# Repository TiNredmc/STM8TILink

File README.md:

# STM8TILink
The TI grey link clone based on arduino code and half duplex code for stm8s (credits after this line). WIP

# credit 
[DSchndr](https://github.com/DSchndr/serial2ti83) fork of [jw0k repo](https://github.com/jw0k/serial2ti83).

# PCB (at OSHpark).
[rev1 PCB](https://oshpark.com/shared_projects/LCwtGfEf).

# Extra
Due to the physical limitation of STM8S001J3 available pin. I was forced to use the single wire bi-directional UART. which it means that I share TX and RX on same pin (based on [This guy work](http://ficara.altervista.org/?p=4047&doing_wp_cron=1633419018.3038520812988281250000)). The problem starts when host send data to CH330N, since the TX is  connected to schottky barrier diode on cathod side, anode side is connected to STM8 (with 4.7k pull up) and RX pin of CH330N. The loopback "echo" occured everytime the host send command to STM8. The CH330N doesn't ignore the RX line when TX is transmitting. SO the host confused that the RX data is valid (which is not!). In order to solve this problem. I redesigned the PCB with included the SN74LVC1G3157DBVR, SPDT analog switch. I use this IC for bus isolation. CH330N RX will be isolated when MCU isn't send any data to host, it will left unconnected all the time to prevent the loopback echo and confuse host device.

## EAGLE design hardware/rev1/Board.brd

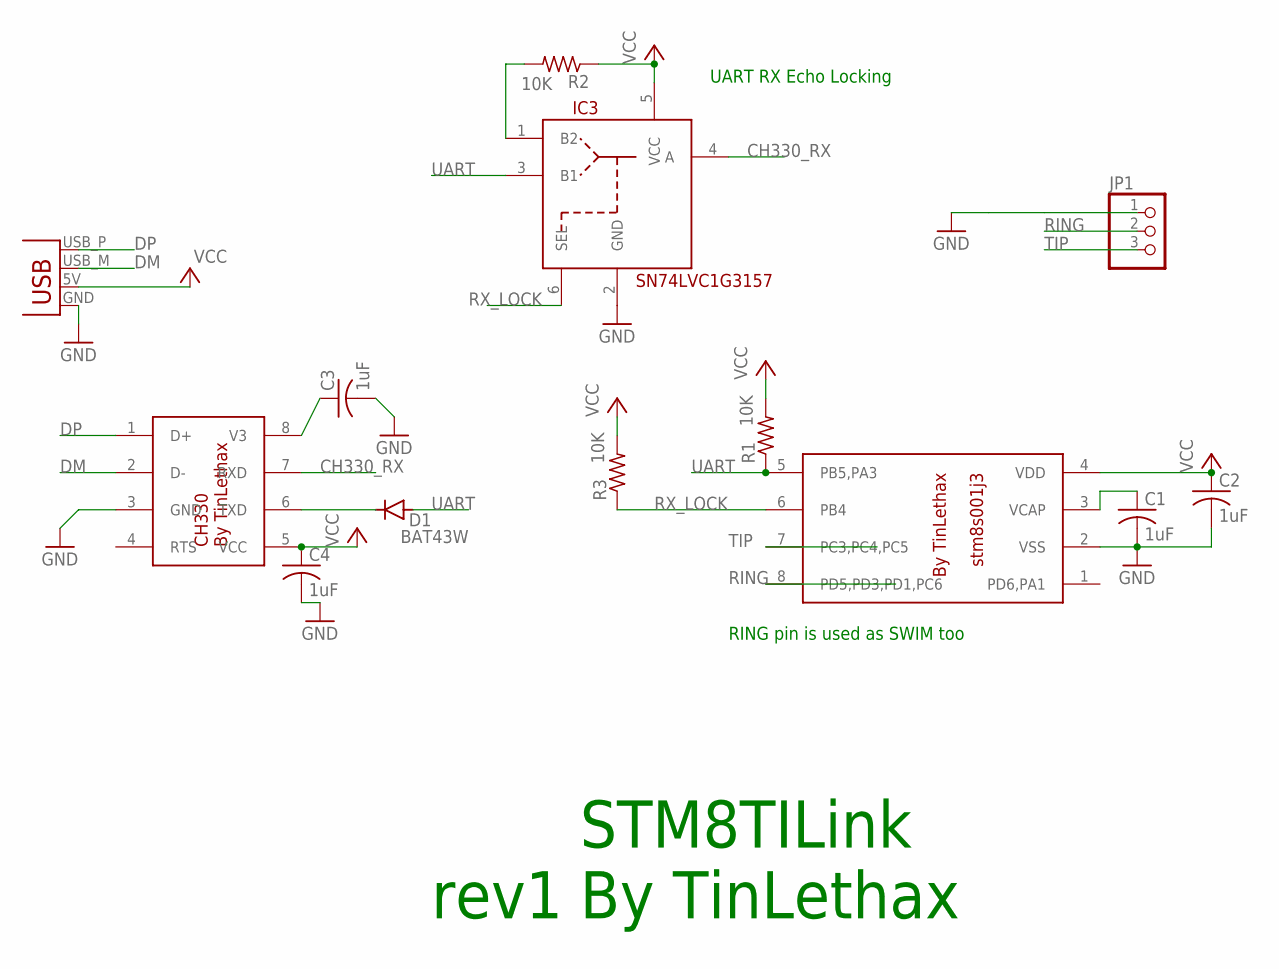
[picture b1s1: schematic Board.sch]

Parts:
C1, C2, C3, C4: 1uF; C0603
D1: BAT43W; SOD-123_MINI-SMA
IC1: STM8S001J3; SOP8
IC2: CH330; SOIC127P600X150-8N
IC3: SN74LVC1G3157; SOT95P280X145-6N
JP1: PINHD-1X3; 1X03
R1, R2, R3: 10K; R0603
X1: USB_USBPCB; USB_USB-A-PCB

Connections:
CH330_RX: IC2.7 (RXD), IC3.4 (A)
DM: IC2.2 (D-), X1.USB_M (D-)
DP: IC2.1 (D+), X1.USB_P (D+)
GND: C1.2, C2.2, C3.2, C4.2, IC1.2 (VSS), IC2.3 (GND), IC3.2 (GND), JP1.1, X1.GND
unnamed: C1.1, IC1.3 (VCAP)
unnamed: IC3.1 (B2), R2.2
unnamed: C3.1, IC2.8 (V3)
unnamed: D1.C, IC2.6 (TXD)
RING: IC1.8 (PD5,PD3,PD1,PC6), JP1.2
RX_LOCK: IC1.6 (PB4), IC3.6 (SEL), R3.1
TIP: IC1.7 (PC3,PC4,PC5), JP1.3
UART: D1.A, IC1.5 (PB5,PA3), IC3.3 (B1), R1.1
VCC: C2.1, C4.1, IC1.4 (VDD), IC2.5 (VCC), IC3.5 (VCC), R1.2, R2.1, R3.2, X1.5V (VBUS)

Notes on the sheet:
STM8TILink By TinLethax
RING pin is used as SWIM too
rev1
UART RX Echo Locking

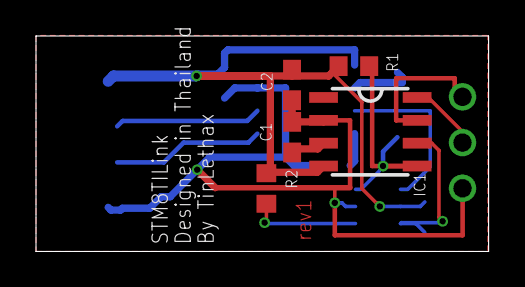
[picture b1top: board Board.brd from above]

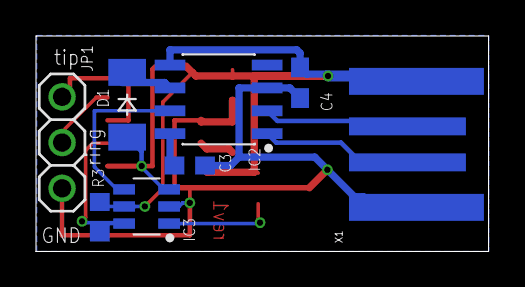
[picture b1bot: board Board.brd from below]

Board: 2 copper layers, 25.1 x 12.0 mm, 13 parts (8 on the bottom side), 13 nets.

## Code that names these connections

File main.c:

////////////////////////////////////////////////////////////////////////////////
// FW_VERSION  180701 (yymmdd) - Author: Emilio P.G. Ficara
// Modified to use with STM8TI by TinLethax
// V180701

#include <stm8s.h> // DO NOT USE here generic iostm8s.h (register map is different)
#include <delay.h>
#include <stdint.h>
#include <stdbool.h>

/* TIM4 stuffs */
// arr value for TIM4 millis() interupt.
#define TOP1MS		124 // Tim4 compare top value for 1mS tick
// millis() return value
volatile uint16_t mil = 0;
uint16_t millis(void);

/* UART stuffs */
volatile uint8_t echo = 0; // flag for "RX data is echo of TX"
volatile uint8_t DataFlag = 0;
volatile uint8_t revDat[4] = {0}; //data receive over the UART

/* variables for TI stuffs */

const uint8_t TIP = 5; //PC5 Tip pin
const uint8_t RING = 6; //PC6 Ring pin
const uint8_t TXTIMEOUT = 70; //50ms
const uint8_t RXTIMEOUT = 40; //20ms


#define TI_TIP_IS_HIGH   (PC_IDR & 0x10) 
#define TI_RING_IS_HIGH (PC_IDR & 0x20)

#define TI_TIP_IS_LOW   (~PC_IDR & 0x10)
#define TI_RING_IS_LOW  (~PC_IDR & 0x20)

void TiTipLow(){
	PC_ODR &= ~(1 << TIP);   
}

void TiRingLow(){
	PC_ODR &= ~(1 << RING);   
}

void TiTipOutput(){
	PC_DDR |= (1 << TIP);
	PC_CR1 |= (1 << TIP);
}

void TiRingOutput(){
	PC_DDR |= (1 << RING);
	PC_CR1 |= (1 << RING);
}

void TiTipInputHigh(){
	PC_DDR &= ~(1 << TIP);
	PC_CR1 |= (1 << TIP);
}

void TiRingInputHigh(){
	PC_DDR &= ~(1 << RING);
	PC_CR1 |= (1 << RING);
}


//------------------------------------------------------------------------------
// Serial COMM section

void OutCom(unsigned char c)// sending single byte from calc to PC
{
	echo = 1; // set echo flag (TX will be immediatly received on RX)
	while((UART1_SR & 0x80) == 0); // wait for TXE = 1
	UART1_DR = c; // send char
	while(echo); // wait until echo received
}

//------------------------------------------------------------------------------
// Interrupts section
//
void tim4_millis_irq(void) __interrupt(23)// The millis part, every 1 ms
{
     TIM4_SR = 0x00; // clear irq flag
     mil++;
}

void USART1_RX(void) __interrupt(18){ // Deal with the incoming data from PC and soon will transfer to calc

uint8_t e;

	e = UART1_SR; // read / clear (and ignore) error flags
	e = 1;
	revDat[0] = UART1_DR; // get the char and clear irq
	if(echo){ // if received data is echo of TX
		echo = 0; // turn off flag and don't save
	}else{
		while(UART1_SR & 0x20)// wait until buffer is empty
		revDat[e++] = UART1_DR;// reading all data from host.
		
		DataFlag = 1;// incoming data is not echo but it's data to send to Ti calc.
	}

}

////////////////////////////////////////////////////////////////////////////////
// Stuff for millis(); and TI stuff
//
uint16_t millis(){
return (uint16_t)mil;
}

void sendByte(uint8_t byte){
    uint16_t currentTime;

    for (uint8_t i = 0; i < 8; ++i){
        bool bit = byte & 0x01;
        byte >>= 1;

        //poll both lines until they are both high, which means we're ready to send a bit
        currentTime = millis();
        while (TI_TIP_IS_LOW || TI_RING_IS_LOW){
            if (millis() - currentTime > TXTIMEOUT){
                return;
            }
        }

        if (bit){
            // send a bit by pulling appropriate line low
            TiRingOutput();
            TiRingLow();

            // wait for opposite line to become low
            currentTime = millis();
            while (TI_TIP_IS_HIGH){
                if (millis() - currentTime > TXTIMEOUT){
                    TiRingInputHigh();// set to input pull up.
                    return;
                }
            }

            // release our line
            TiRingInputHigh();

            // wait for opposite line to become high
            currentTime = millis();
            while (TI_TIP_IS_LOW){
                if (millis() - currentTime > TXTIMEOUT){
                    return;
                }
            }

        }else{
            // send a bit by pulling appropriate line low
            TiTipOutput();
            TiTipLow();

            // wait for opposite line to become low
            currentTime = millis();
            while (TI_RING_IS_HIGH){
                if (millis() - currentTime > TXTIMEOUT){
                    TiTipInputHigh();
                    return;
                }
            }

            // release our line
            TiTipInputHigh();

            // wait for opposite line to become high
            currentTime = millis();
            while (TI_RING_IS_LOW){
                if (millis() - currentTime > TXTIMEOUT){
                    return;
                }
            }

        }
  }
}

bool getByte(uint8_t *byte){
   uint16_t currentTime;
    uint8_t result = 0;
    for (uint8_t i = 0; i < 8; ++i)
    {

        currentTime = millis();
        while (TI_RING_IS_HIGH && TI_TIP_IS_HIGH)
        {
            if (millis() - currentTime > RXTIMEOUT)
            {
                return false;
            }
        }
        
        bool bit = TI_RING_IS_LOW;
        result >>= 1;
        
        if (bit)
        {
            //ourLine = TIP;
            //oppositeLine = RING;
            result |= 0x80; //bits are always transmitted LSb first (least significant bit)
            
            // acknowledge a bit by pulling appropriate line low
            TiTipOutput();
            TiTipLow();
            
            //wait for opposite line to become high
            currentTime = millis();
            while (TI_RING_IS_LOW)
            {
                if (millis() - currentTime > RXTIMEOUT)
                {
                    TiTipInputHigh();// Set to input pull-up mode
                    return false;
                }
            }

            // release our line
            TiTipInputHigh();
        }
        else
        {
            //ourLine = RING;
            //oppositeLine = TIP;
            
            // acknowledge a bit by pulling appropriate line low
            TiRingOutput();
            TiRingLow();
            
            //wait for opposite line to become high
            while (TI_TIP_IS_LOW)
            {
                if (millis() - currentTime > RXTIMEOUT)
                {
                    TiRingInputHigh();

                }
            }

            // release our line
            TiRingInputHigh();// set input pull up.
            
        }
    }

    *byte = result;
return true;

}

void main(void)
{
	CLK_CKDIVR = 0x00;  // Set the frequency to 16 MHz

	delay_ms(1000);// startup delay for SWIM programming before take over the SWIM pin for other usage.

	PA_ODR |= 0x08; // 0000.1000 All PA data is 0 except PA3 (UART_TX)
	PA_DDR |= 0x08; // 0000.1000 PA.3 is output
	PA_CR1 |= 0x00; // 0000.0000 PA.3 is open drain

	PB_DDR |= (1 << 4);// PB 4 as output open-drain
	PB_ODR |= (1 << 4);// immediately release pull down. 

   	 //configure both lines as input and enable pull-up resistors
	//PC_DDR = (0 << TIP) | (0 << RING);
	PC_CR1 |= (1 << TIP) | (1 << RING);
	//PC_CR2 = (0 << TIP) | (0 << RING); 

	// init the uart1 in the single pin half duplex mode on PA3 (pin 5 on SOP8)
	UART1_CR1 = 0x00; // 0000.0000 Enable UART 8bit, no parity
	UART1_CR3 = 0x00; // 0000.0000 1 stop bit
	UART1_CR5 = 0x08; // 0000.1000 no dma, half duplex
	UART1_BRR2 = 0x03; // set 9600 BPS
	UART1_BRR1 = 0x68; //
	UART1_CR2 = 0x2C; // 0010.1100 Enable RX irq, Enable TX and RX

	// Timer4 setup for millis()-likes function.
	TIM4_PSCR = 0x07; // fCK_CNT = fCK_PSC/2**PSCR (2**7=128)
	TIM4_ARR = TOP1MS; // set TOP value (reset cnt) for 1mS
	TIM4_SR = 0x00;
	TIM4_IER |= 0x01;
	TIM4_CR1 |= 0x01;

  	 __asm__("rim");

	while(1){
		while(DataFlag){
			sendByte(revDat[0]);
			sendByte(revDat[1]);
			sendByte(revDat[2]);
			sendByte(revDat[3]);	
			DataFlag = 0;// clear data receipt flag.
		}

		uint8_t byteFromCalc = 0;
		if (getByte(&byteFromCalc)){
			PB_ODR &= ~(1 << 4);// pull low to switch from B2 to B1 and connect CH330's RX to MCU pin.
			OutCom(byteFromCalc);
			PB_ODR |= (1 << 4);// release to switch back to B2 (has a pul up for CH330's RX pin).
		}
	}
}

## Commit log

2021-10-04 Added source file for STM8S001J3.
2021-10-04 [W.I.P.] added RX lock.
2021-10-05 Added more things to it.
2021-10-05 added BOMs
2021-10-05 Schematic and Board file
2021-10-05 Rename REV1.MD to REV1.md
2021-10-05 Rename REV1.md to README.md
